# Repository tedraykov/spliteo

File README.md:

# Spliteo

Ergonomic split keyboard with a 3x6 matrix layout and a 4 key thumb cluster.

## Bill of Materials

| Part                                                 | Quantity | Estimated Price | Source                                                                                                                                                                                    |
| ---------------------------------------------------- | -------- | --------------- | ----------------------------------------------------------------------------------------------------------------------------------------------------------------------------------------- |
| Custom PCB                                           | 1        | 9.06$           | https://jlcpcb.com                                                                                                                                                                        |
| Low-profile Keycaps                                  | 1 set    | 19.44$          | https://item.taobao.com/item.htm?id=873448851434                                                                                                                                          |
| Hot-swappable switch connector (Choc v2 - 1350/1353) | 44       | 8.08$           | https://detail.tmall.com/item.htm?id=640063427738                                                                                                                                         |
| Kailh Full POM Black cloud                           | 44       | 24.22$          | https://detail.tmall.com/item.htm?id=813618264203                                                                                                                                         |
| Promicro Nrf52840 (Compatible with Nice!Nano V2.0)   | 2        | 4.22$           | https://item.taobao.com/item.htm?id=799443140168                                                                                                                                          |
| Switch                                               | 2        |                 | https://vikiwat.com/prevklyuchvatel-2poz-03a-4vdc-spdt?_gl=1*1ycxpf8*_up*MQ..*_gs*MQ..&gclid=Cj0KCQjwtJ6_BhDWARIsAGanmKfTHJL2aIPRrds-LOpXbn-6GezxabXCETT-lDOsea4CDu5uTdaZ-T0aAu2pEALw_wcB |
|                                                      |          |                 |                                                                                                                                                                                           |
| Shipping Costs                                       | -        | 30,98$          | https://www.acbuy.com                                                                                                                                                                     |
| **Total**                                            |          | **96.00$**      |                                                                                                                                                                                           |

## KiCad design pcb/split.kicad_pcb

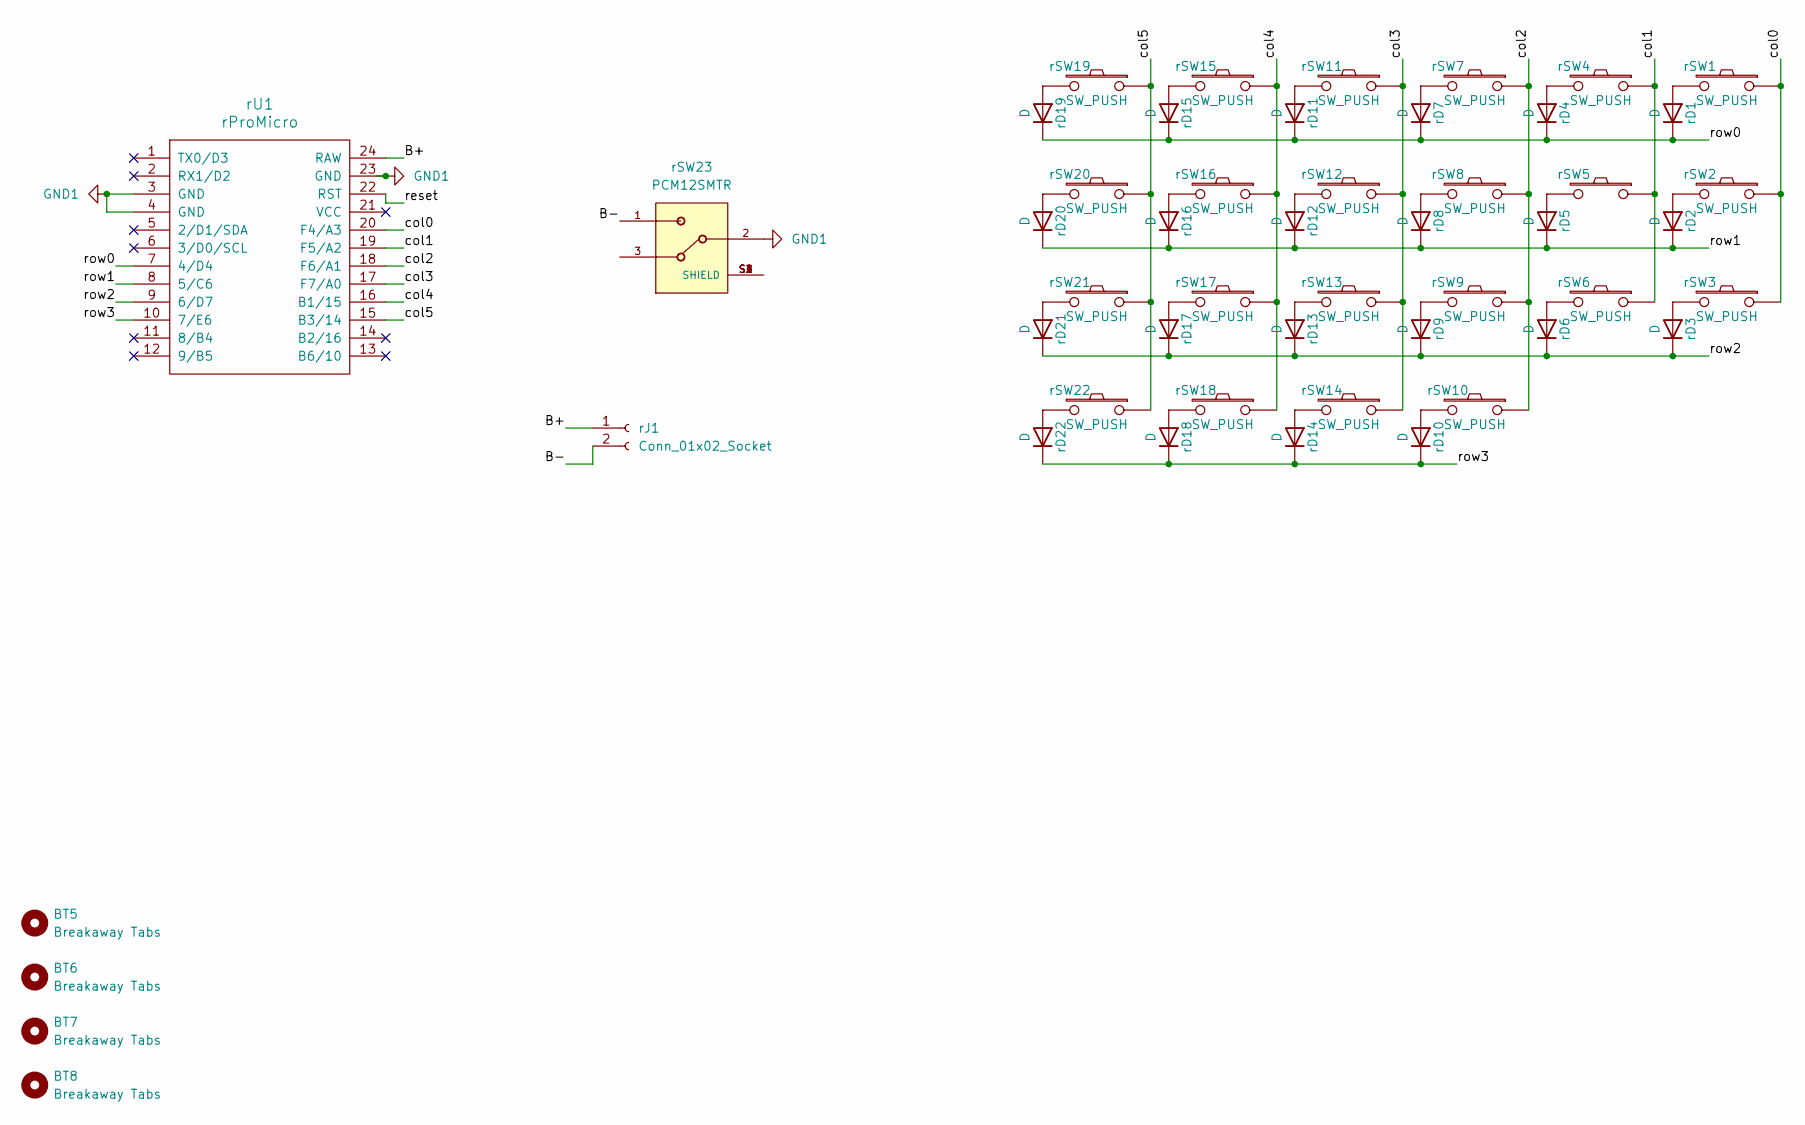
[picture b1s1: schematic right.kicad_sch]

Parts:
BT5, BT6, BT7, BT8: Breakaway Tabs; Breakaway_Tabs
rD1, rD2, rD3, rD4, rD5, rD6, rD7, rD8, rD9, rD10, rD11, rD12, rD13, rD14, rD15, rD16, rD17, rD18, rD19, rD20, rD21, rD22: D; Nexperia_CFP3_SOD-123W
rJ1: Conn_01x02_Socket; JST_EH_S2B-EH_1x02_P2.50mm_Horizontal
rSW1, rSW2, rSW3, rSW4, rSW5, rSW6, rSW7, rSW8, rSW9, rSW10, rSW11, rSW12, rSW13, rSW14, rSW15, rSW16, rSW17, rSW18, rSW19, rSW20, rSW21, rSW22: SW_PUSH; keyswitch_choc12_hotswap_1u
rSW23: PCM12SMTR; SW_SPDT_PCM12
rU1: rProMicro; ProMicro

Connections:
/Right/B+: rJ1.1, rU1.24 (RAW)
/Right/B-: rJ1.2, rSW23.1
/Right/col0: rSW1.1, rSW2.1, rSW3.1, rU1.20 (F4/A3)
/Right/col1: rSW4.1, rSW5.1, rSW6.1, rU1.19 (F5/A2)
/Right/col2: rSW7.1, rSW8.1, rSW9.1, rSW10.1, rU1.18 (F6/A1)
/Right/col3: rSW11.1, rSW12.1, rSW13.1, rSW14.1, rU1.17 (F7/A0)
/Right/col4: rSW15.1, rSW16.1, rSW17.1, rSW18.1, rU1.16 (B1/15)
/Right/col5: rSW19.1, rSW20.1, rSW21.1, rSW22.1, rU1.15 (B3/14)
/Right/reset: rU1.22 (RST)
/Right/row0: rD1.1 (K), rD4.1 (K), rD7.1 (K), rD11.1 (K), rD15.1 (K), rD19.1 (K), rU1.7 (4/D4)
/Right/row1: rD2.1 (K), rD5.1 (K), rD8.1 (K), rD12.1 (K), rD16.1 (K), rD20.1 (K), rU1.8 (5/C6)
/Right/row2: rD3.1 (K), rD6.1 (K), rD9.1 (K), rD13.1 (K), rD17.1 (K), rD21.1 (K), rU1.9 (6/D7)
/Right/row3: rD10.1 (K), rD14.1 (K), rD18.1 (K), rD22.1 (K), rU1.10 (7/E6)
GND1: rSW23.2, rU1.3 (GND), rU1.4 (GND), rU1.23 (GND)
unnamed: rD1.2 (A), rSW1.2
unnamed: rD2.2 (A), rSW2.2
unnamed: rD3.2 (A), rSW3.2
unnamed: rD4.2 (A), rSW4.2
unnamed: rD5.2 (A), rSW5.2
unnamed: rD6.2 (A), rSW6.2
unnamed: rD7.2 (A), rSW7.2
unnamed: rD8.2 (A), rSW8.2
unnamed: rD9.2 (A), rSW9.2
unnamed: rD10.2 (A), rSW10.2
unnamed: rD11.2 (A), rSW11.2
unnamed: rD12.2 (A), rSW12.2
unnamed: rD13.2 (A), rSW13.2
unnamed: rD14.2 (A), rSW14.2
unnamed: rD15.2 (A), rSW15.2
unnamed: rD16.2 (A), rSW16.2
unnamed: rD17.2 (A), rSW17.2
unnamed: rD18.2 (A), rSW18.2
unnamed: rD19.2 (A), rSW19.2
unnamed: rD20.2 (A), rSW20.2
unnamed: rD21.2 (A), rSW21.2
unnamed: rD22.2 (A), rSW22.2

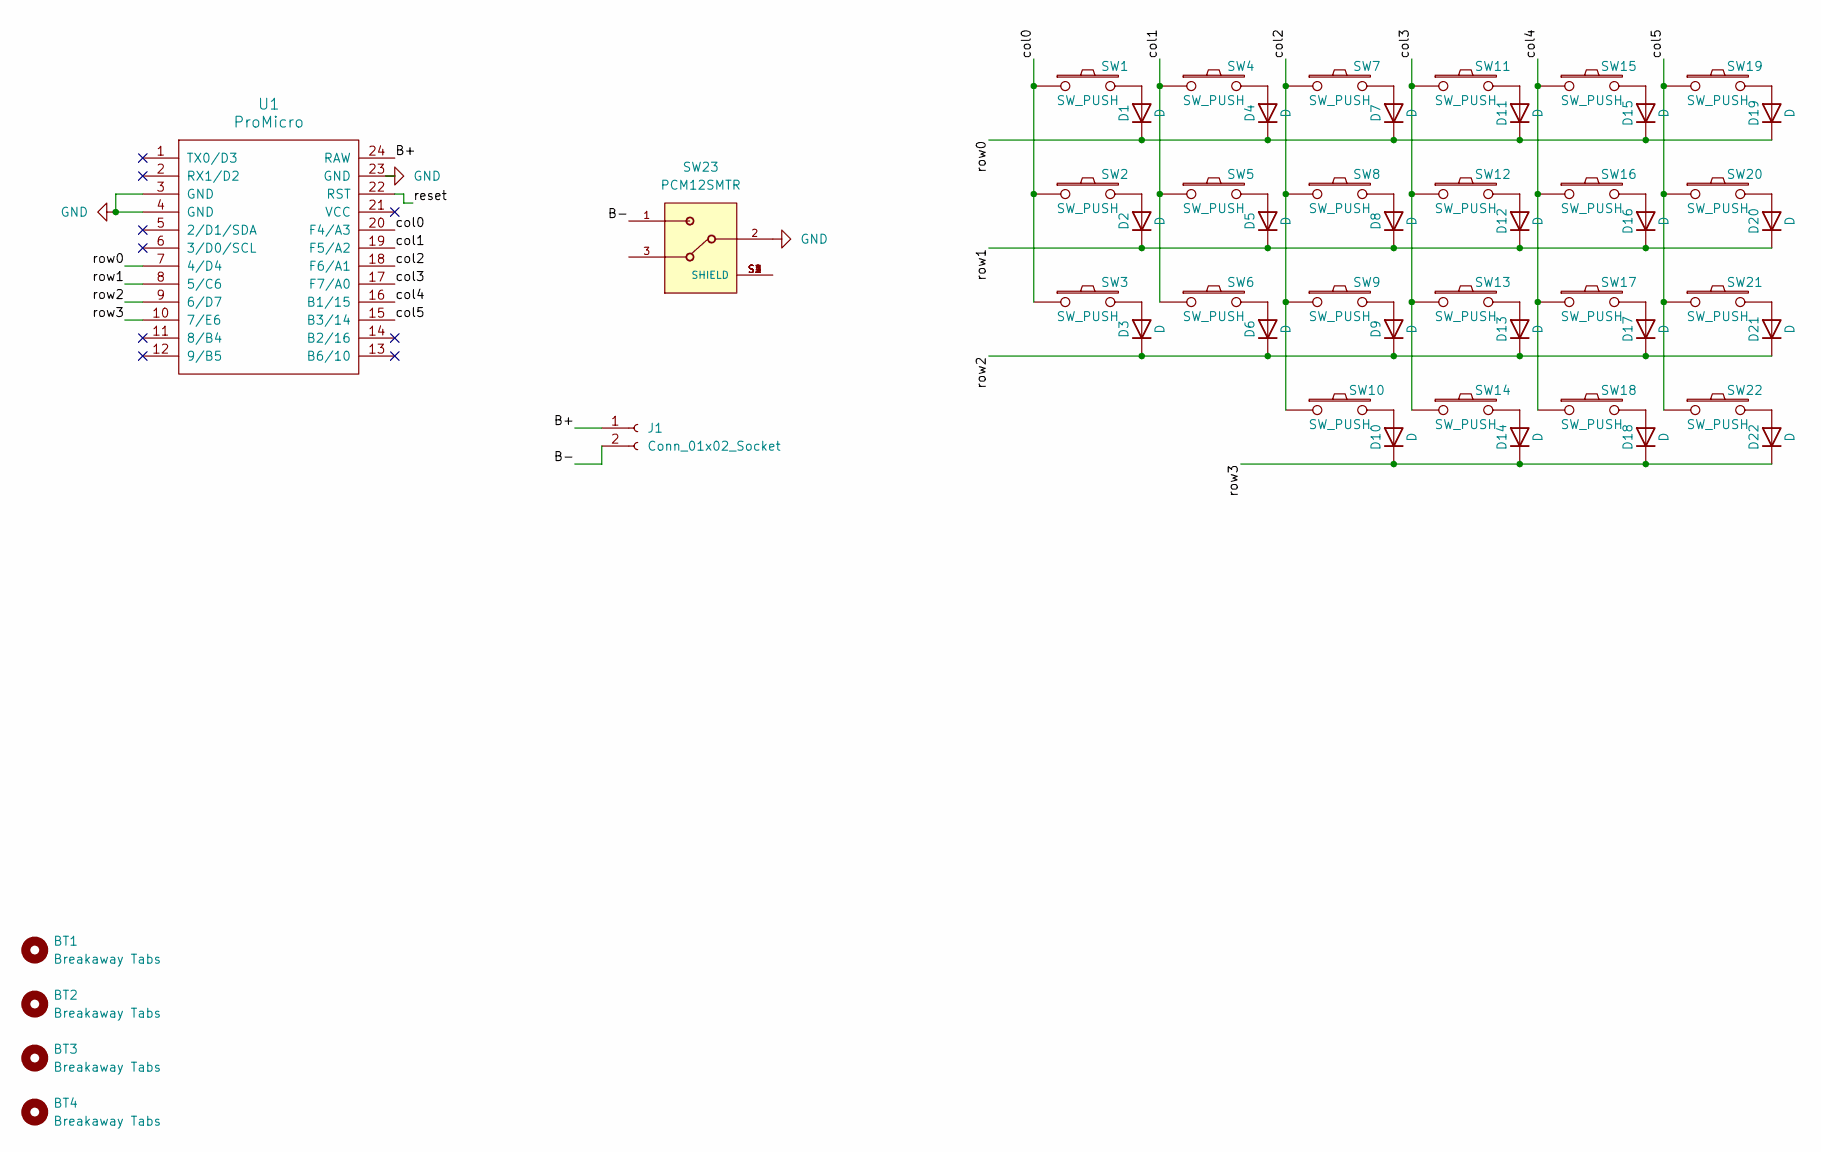
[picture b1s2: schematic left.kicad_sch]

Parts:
BT1, BT2, BT3, BT4: Breakaway Tabs; Breakaway_Tabs
D1, D2, D3, D4, D5, D6, D7, D8, D9, D10, D11, D12, D13, D14, D15, D16, D17, D18, D19, D20, D21, D22: D; Nexperia_CFP3_SOD-123W
J1: Conn_01x02_Socket; JST_EH_S2B-EH_1x02_P2.50mm_Horizontal
SW1, SW2, SW3, SW4, SW5, SW6, SW7, SW8, SW9, SW10, SW11, SW12, SW13, SW14, SW15, SW16, SW17, SW18, SW19, SW20, SW21, SW22: SW_PUSH; keyswitch_choc12_hotswap_1u
SW23: PCM12SMTR; SW_SPDT_PCM12
U1: ProMicro

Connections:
/Left/B+: J1.1, U1.24 (RAW)
/Left/B-: J1.2, SW23.1
/Left/col0: SW1.1, SW2.1, SW3.1, U1.20 (F4/A3)
/Left/col1: SW4.1, SW5.1, SW6.1, U1.19 (F5/A2)
/Left/col2: SW7.1, SW8.1, SW9.1, SW10.1, U1.18 (F6/A1)
/Left/col3: SW11.1, SW12.1, SW13.1, SW14.1, U1.17 (F7/A0)
/Left/col4: SW15.1, SW16.1, SW17.1, SW18.1, U1.16 (B1/15)
/Left/col5: SW19.1, SW20.1, SW21.1, SW22.1, U1.15 (B3/14)
/Left/reset: U1.22 (RST)
/Left/row0: D1.1 (K), D4.1 (K), D7.1 (K), D11.1 (K), D15.1 (K), D19.1 (K), U1.7 (4/D4)
/Left/row1: D2.1 (K), D5.1 (K), D8.1 (K), D12.1 (K), D16.1 (K), D20.1 (K), U1.8 (5/C6)
/Left/row2: D3.1 (K), D6.1 (K), D9.1 (K), D13.1 (K), D17.1 (K), D21.1 (K), U1.9 (6/D7)
/Left/row3: D10.1 (K), D14.1 (K), D18.1 (K), D22.1 (K), U1.10 (7/E6)
GND: SW23.2, U1.3 (GND), U1.4 (GND), U1.23 (GND)
unnamed: D1.2 (A), SW1.2
unnamed: D2.2 (A), SW2.2
unnamed: D3.2 (A), SW3.2
unnamed: D4.2 (A), SW4.2
unnamed: D5.2 (A), SW5.2
unnamed: D6.2 (A), SW6.2
unnamed: D7.2 (A), SW7.2
unnamed: D8.2 (A), SW8.2
unnamed: D9.2 (A), SW9.2
unnamed: D10.2 (A), SW10.2
unnamed: D11.2 (A), SW11.2
unnamed: D12.2 (A), SW12.2
unnamed: D13.2 (A), SW13.2
unnamed: D14.2 (A), SW14.2
unnamed: D15.2 (A), SW15.2
unnamed: D16.2 (A), SW16.2
unnamed: D17.2 (A), SW17.2
unnamed: D18.2 (A), SW18.2
unnamed: D19.2 (A), SW19.2
unnamed: D20.2 (A), SW20.2
unnamed: D21.2 (A), SW21.2
unnamed: D22.2 (A), SW22.2

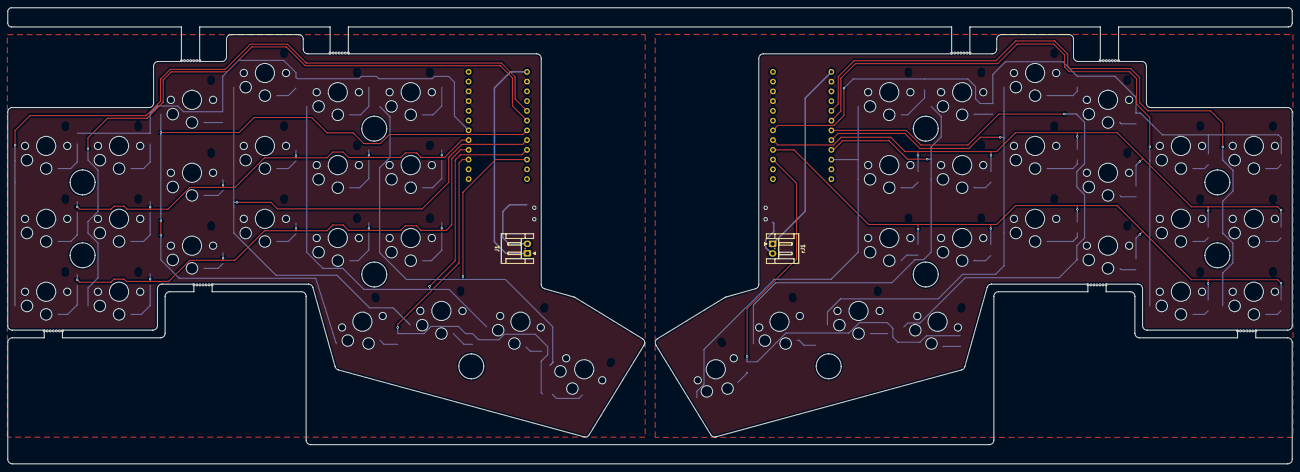
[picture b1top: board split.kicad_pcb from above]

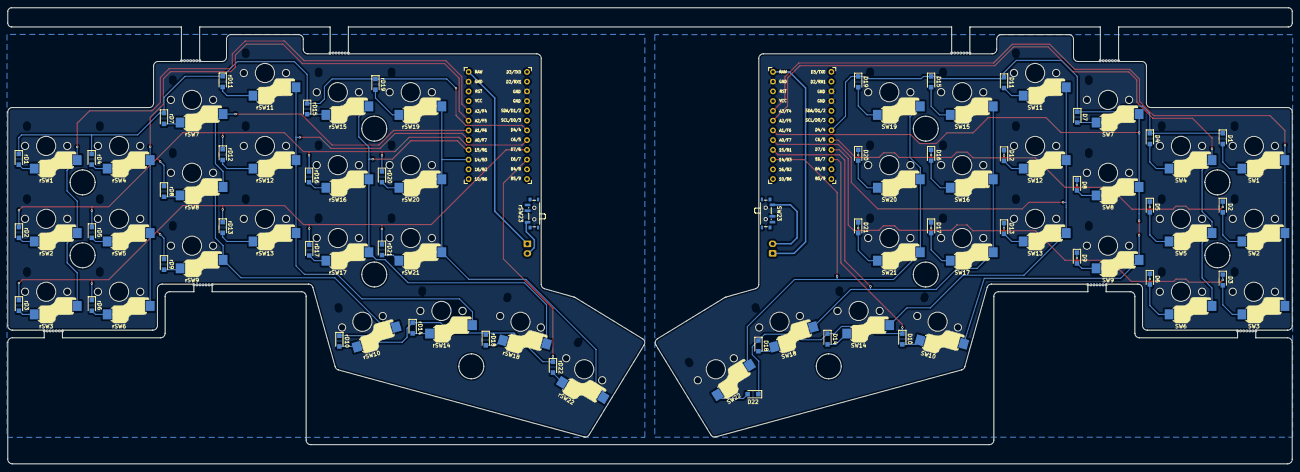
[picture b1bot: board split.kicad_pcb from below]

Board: 2 copper layers, 334.7 x 118.8 mm, 102 parts (92 on the bottom side), 70 nets.

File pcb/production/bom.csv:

Designator,Footprint,Quantity,Value,LCSC Part #
"BT1, BT2, BT3, BT4, BT5, BT6, BT7, BT8",Breakaway_Tabs,8,Breakaway Tabs,
"D1, D10, D11, D12, D13, D14, D15, D16, D17, D18, D19, D2, D20, D21, D22, D3, D4, D5, D6, D7, D8, D9, RD1, RD10, RD11, RD12, RD13, RD14, RD15, RD16, RD17, RD18, RD19, RD2, RD20, RD21, RD22, RD3, RD4, RD5, RD6, RD7, RD8, RD9",Nexperia_CFP3_SOD-123W,44,D,
"J1, RJ1",JST_EH_S2B-EH_1x02_P2.50mm_Horizontal,2,Conn_01x02_Socket,
"RSW1, RSW10, RSW11, RSW12, RSW13, RSW14, RSW15, RSW16, RSW17, RSW18, RSW19, RSW2, RSW20, RSW21, RSW22, RSW3, RSW4, RSW5, RSW6, RSW7, RSW8, RSW9, SW1, SW10, SW11, SW12, SW13, SW14, SW15, SW16, SW17, SW18, SW19, SW2, SW20, SW21, SW22, SW3, SW4, SW5, SW6, SW7, SW8, SW9",keyswitch_choc12_hotswap_1u,44,SW_PUSH,
"RSW23, SW23",SW_SPDT_PCM12,2,PCM12SMTR,
RU1,ProMicro,1,rProMicro,
U1,ProMicro,1,ProMicro,

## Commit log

2025-03-04 Add low-profile pcb for choc v2 switches
2025-03-08 add latest pcb with breakaway tabs
2025-03-08 add production files and readme
2025-03-29 add BOM
2025-05-02 add fusion file
